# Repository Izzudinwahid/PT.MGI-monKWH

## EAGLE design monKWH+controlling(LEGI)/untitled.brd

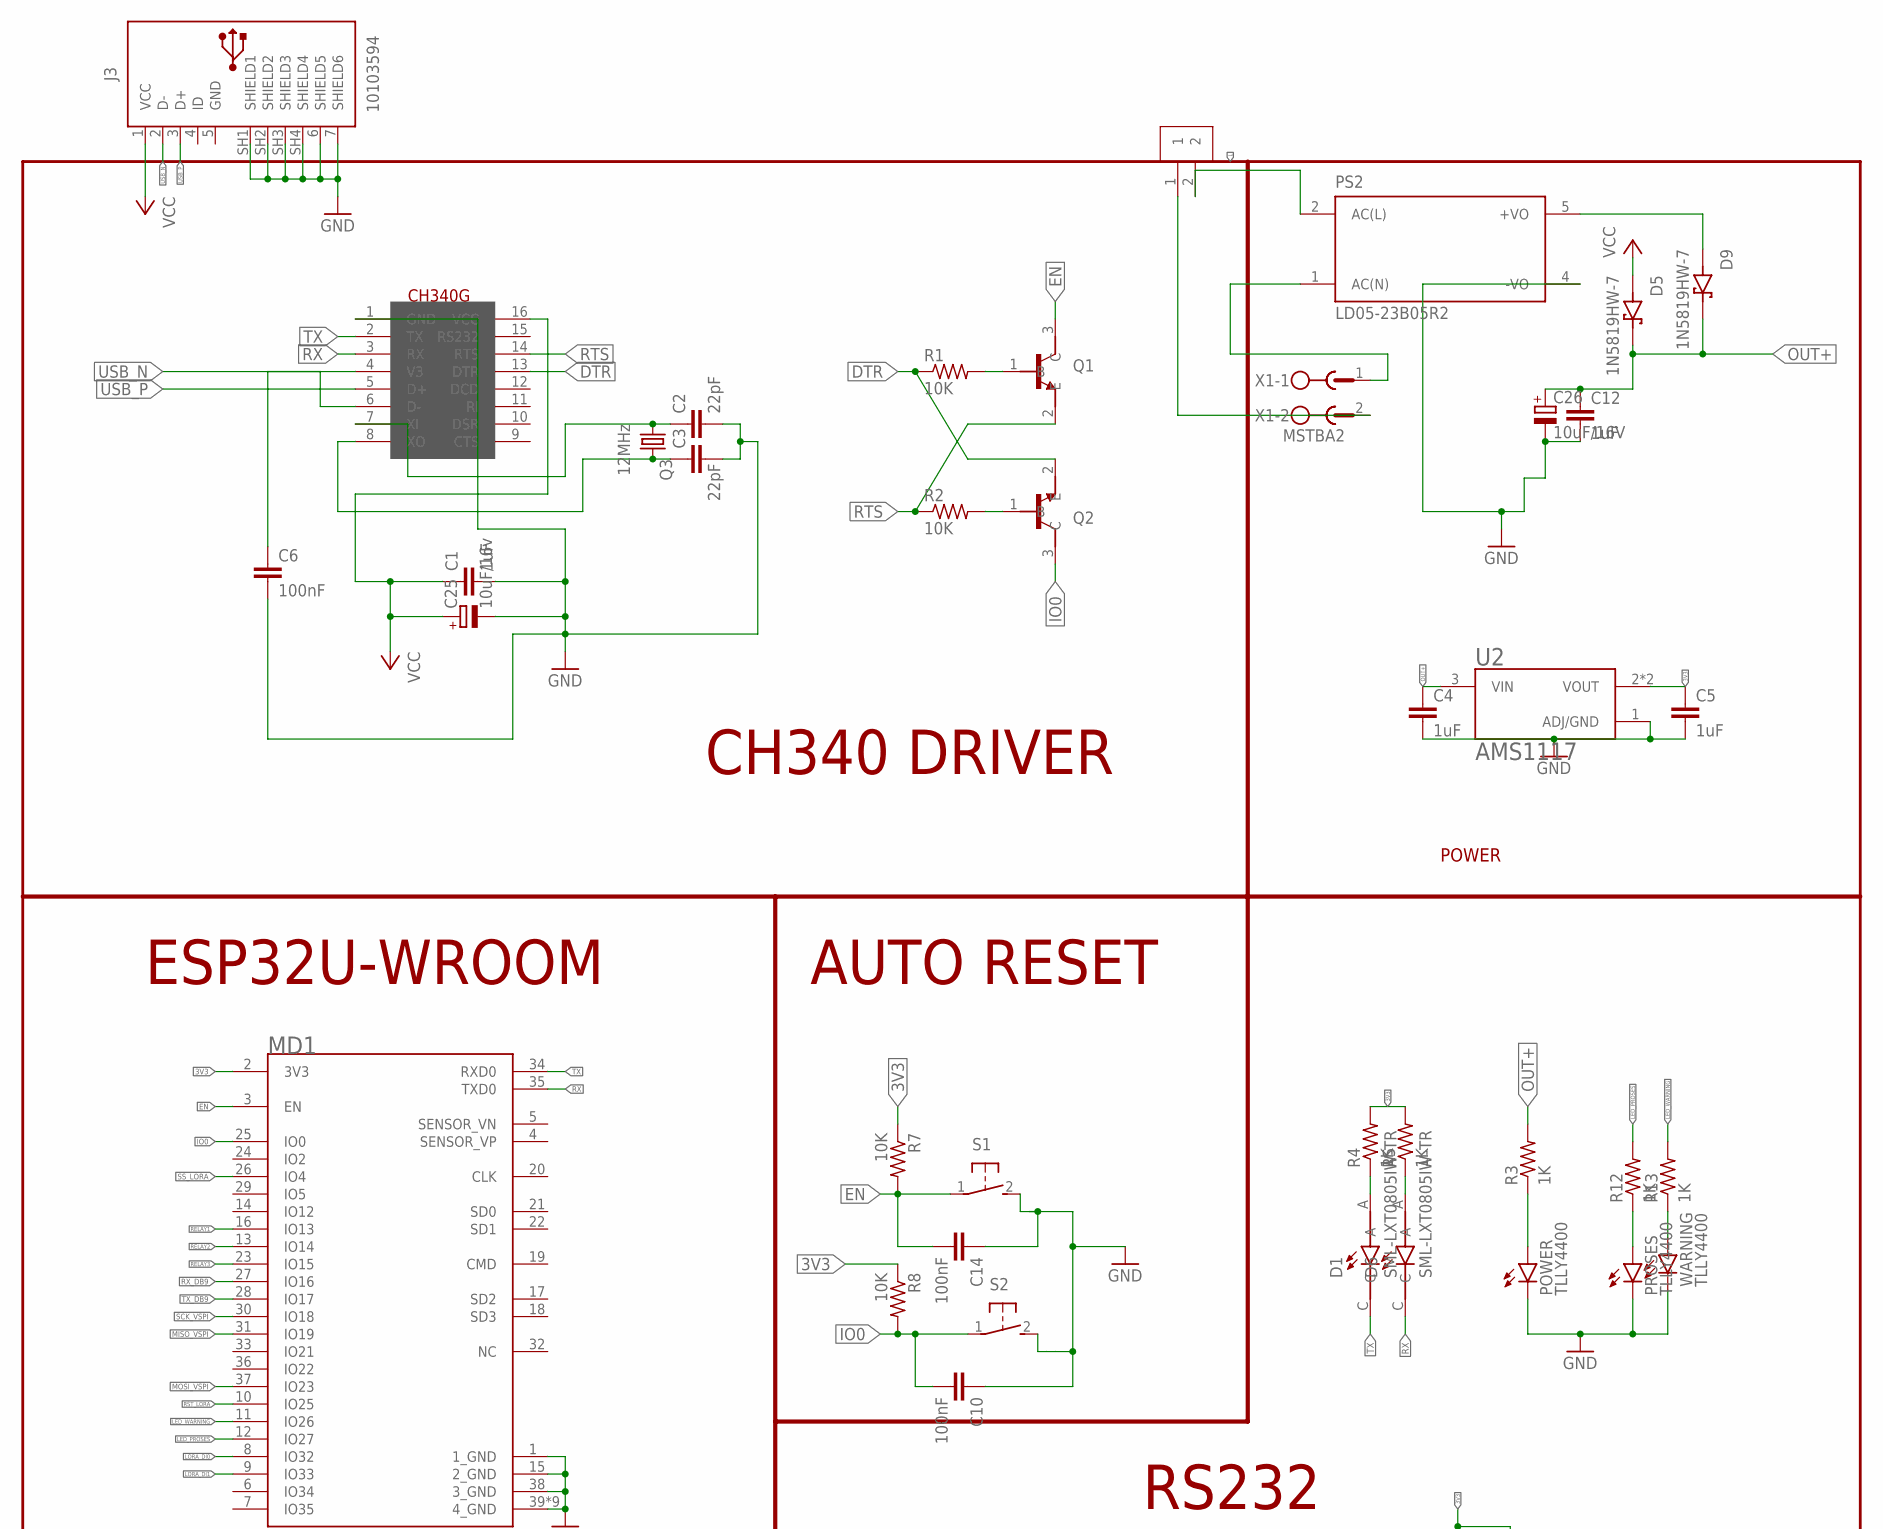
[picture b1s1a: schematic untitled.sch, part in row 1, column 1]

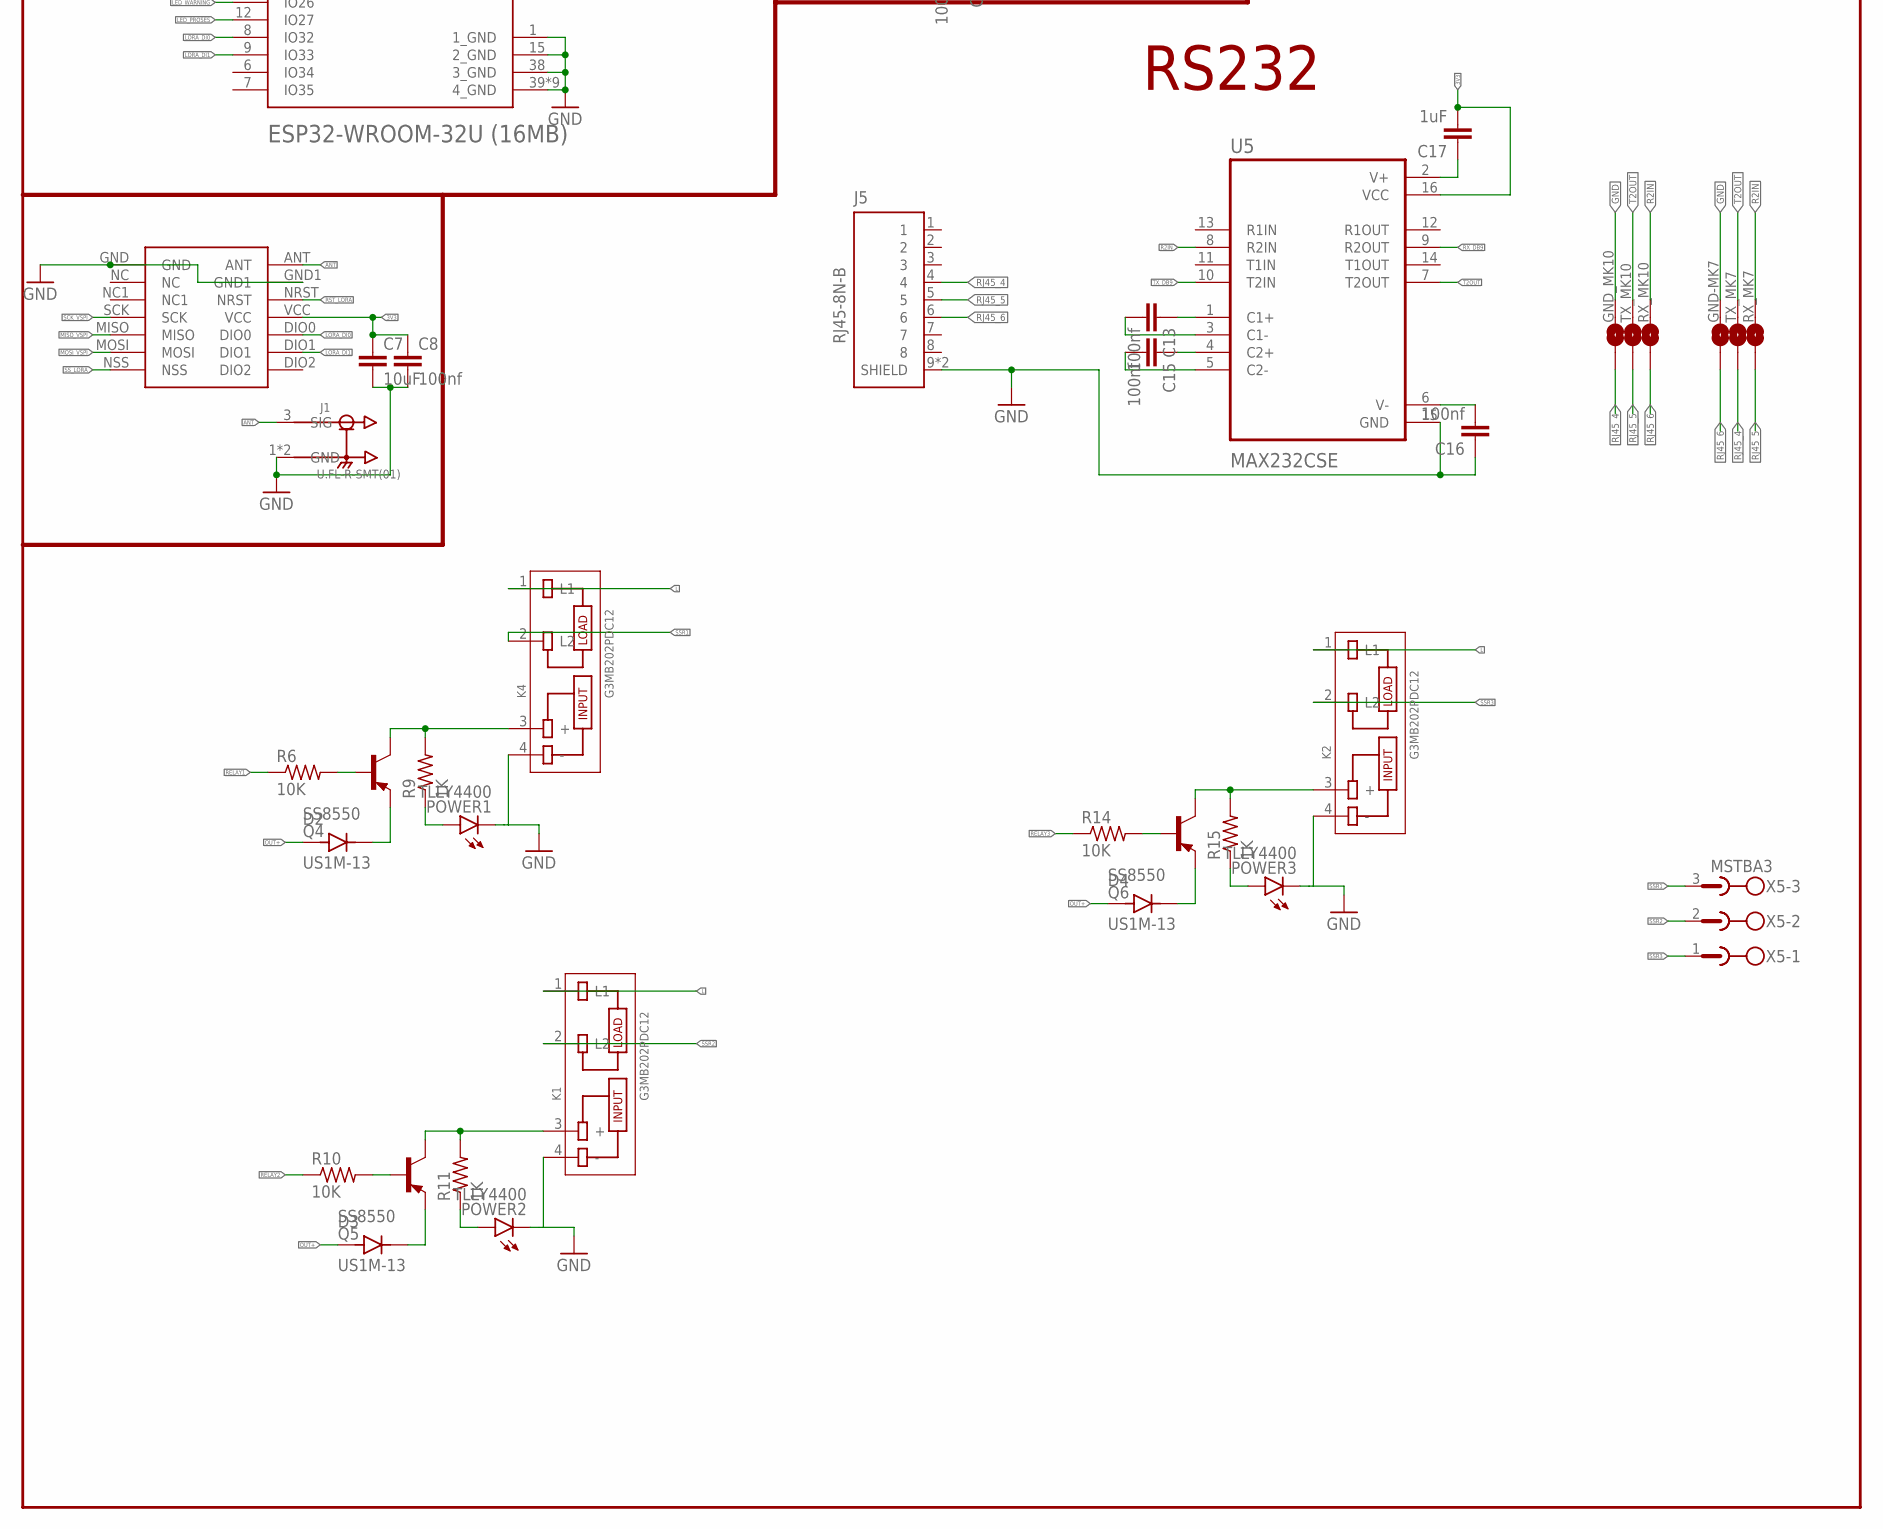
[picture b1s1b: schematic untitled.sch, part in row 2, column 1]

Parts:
C1, C4, C5, C12: 1uF; C0805K
C2, C3: 22pF; C0805K
C6, C10, C14: 100nF; C0805K
C7: 10uF; C0805
C8, C13, C15, C16: 100nf; C0805
C17: 1uF; C0805
C25: 10uF/16v; 153CLV-0505
C26: 10uF/16V; 153CLV-0505
D1, D6: SML-LXT0805IW-TR; LEDC2012X120N
D2, D3, D4: US1M-13; DIOM5226X240N
D5, D9: 1N5819HW-7; SOD3715X145N
FUSE-KOTAK1: FUSE-KOTAK
GND-MK7: 1X02-SJ-NO
GND_MK10: 1X02-SJ-NO
J1: U.FL-R-SMT(01); HRS_U.FL-R-SMT(01)
J3: 10103594
J5: RJ45-8N-B; TE_RJ45-8N-B
K1, K2, K4: G3MB202PDC12; RELAY_G3MB202PDC12
LORA-NICERF-V1: LORA-NICERF-V2
MD1: ESPRESSIF_SYSTEMS_ESP32-WROOM-32U_16MBESPRESSIF_S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; ESPRESSIF_SYSTEMS_ESP32-WROOM-32U_16MB_0
POWER, POWER1, POWER2, POWER3: TLLY4400; LED3MM
PROSES: TLLY4400; LED3MM
PS2: LD05-23B05R2; CONV_LD05-23B05R2
Q1, Q2: MMBT3904; SOT95P240X120-3N
Q3: 12MHz; SM49
Q4, Q5, Q6: SS8550; SOT-23_BEC
R1, R2, R6, R7, R8, R10, R14: 10K; M0805
R3, R4, R5, R9, R11, R12, R13, R15: 1K; M0805
RX_MK7, RX_MK10: 1X02-SJ-NO
S1, S2: 31-XX; B3F-31XX
TX_MK7, TX_MK10: 1X02-SJ-NO
U2: AMS1117; SOT229P700X180-4N
U5: MAX232CSE; SOIC127P600X175-16N
U$2: CH340G; SOIC16
WARNING: TLLY4400; LED3MM
X1: MSTBA2
X5: MSTBA3

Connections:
3V3: C5.1, C7.1, C8.1, C17.2, LORA-NICERF-V1.VCC, MD1.2 (3V3), R4.2, R5.2, R7.1, R8.1, U2.2 (VOUT), U2.4 (VOUT), U5.16 (VCC)
ANT: J1.3 (SIG), LORA-NICERF-V1.ANT
DTR: Q2.2 (E), R1.1, U$2.13 (DTR)
EN: C14.2, MD1.3 (EN), Q1.3 (C), R7.2, S1.1
GND: C1.2, C2.2, C3.2, C4.2, C5.2, C6.2, C7.2, C8.2, C10.1, C12.2, C14.1, C16.1, C25.-, C26.-, GND-MK7.2, GND_MK10.2, J1.1 (GND), J1.2 (GND), J3.5 (GND), J3.6 (SHIELD5), J3.7 (SHIELD6), J3.SH1 (SHIELD1), J3.SH2 (SHIELD2), J3.SH3 (SHIELD3), J3.SH4 (SHIELD4), J5.9 (SHIELD), J5.10 (SHIELD), K1.4 (-), K2.4 (-), K4.4 (-), LORA-NICERF-V1.GND, LORA-NICERF-V1.GND1, MD1.1 (1_GND), MD1.15 (2_GND), MD1.38 (3_GND), MD1.39 (4_GND), MD1.39-2 (4_GND), MD1.39-3 (4_GND), MD1.39-4 (4_GND), MD1.39-5 (4_GND), MD1.39-6 (4_GND), MD1.39-7 (4_GND), MD1.39-8 (4_GND), MD1.39-9 (4_GND), POWER.K (C), POWER1.K (C), POWER2.K (C), POWER3.K (C), PROSES.K (C), PS2.4 (-VO), S1.2 (S), S2.2 (S), U2.1 (ADJ/GND), U5.15 (GND), U$2.1 (GND), WARNING.K (C)
IO0: C10.2, MD1.25 (IO0), Q2.3 (C), R8.2, S2.1
L: FUSE-KOTAK1.2, K1.1 (L1), K2.1 (L1), K4.1 (L1), PS2.2 (AC(L))
LED_PROSES: MD1.12 (IO27), R12.2
LED_WARNING: MD1.11 (IO26), R13.2
LORA_DI0: LORA-NICERF-V1.DIO0, MD1.8 (IO32)
LORA_DI1: LORA-NICERF-V1.DIO1, MD1.9 (IO33)
MISO_VSPI: LORA-NICERF-V1.MISO, MD1.31 (IO19)
MOSI_VSPI: LORA-NICERF-V1.MOSI, MD1.37 (IO23)
unnamed: C2.1, Q3.1, U$2.7 (XI)
unnamed: C3.1, Q3.2, U$2.8 (XO)
unnamed: POWER.A, R3.1
unnamed: Q1.1 (B), R1.2
unnamed: Q2.1 (B), R2.2
unnamed: D2.C (K), Q4.E
unnamed: Q4.B, R6.2
unnamed: D1.A, R4.1
unnamed: D6.A, R5.1
unnamed: C13.1, U5.1 (C1+)
unnamed: PS2.1 (AC(N)), X1.1
unnamed: C6.1, U$2.4 (V3)
unnamed: C13.2, U5.3 (C1-)
unnamed: K4.3 (+), Q4.C, R9.2
unnamed: D9.A, PS2.5 (+VO)
unnamed: FUSE-KOTAK1.1, X1.2
unnamed: POWER1.A, R9.1
unnamed: C15.1, U5.4 (C2+)
unnamed: D3.C (K), Q5.E
unnamed: Q5.B, R10.2
unnamed: C15.2, U5.5 (C2-)
unnamed: PROSES.A, R12.1
unnamed: C17.1, U5.2 (V+)
unnamed: C16.2, U5.6 (V-)
unnamed: R13.1, WARNING.A
unnamed: K1.3 (+), Q5.C, R11.2
unnamed: POWER2.A, R11.1
unnamed: D4.C (K), Q6.E
unnamed: Q6.B, R14.2
unnamed: K2.3 (+), Q6.C, R15.2
unnamed: POWER3.A, R15.1
OUT+: C4.1, C12.1, C26.+, D2.A, D3.A, D4.A, D5.C (K), D9.C (K), R3.2, U2.3 (VIN)
R2IN: RX_MK7.2, RX_MK10.2, U5.8 (R2IN)
RELAY1: MD1.16 (IO13), R6.1
RELAY2: MD1.13 (IO14), R10.1
RELAY3: MD1.23 (IO15), R14.1
RJ45_4: GND_MK10.1, J5.4, TX_MK7.1
RJ45_5: J5.5, RX_MK7.1, TX_MK10.1
RJ45_6: GND-MK7.1, J5.6, RX_MK10.1
RST_LORA: LORA-NICERF-V1.NRST, MD1.10 (IO25)
RTS: Q1.2 (E), R2.1, U$2.14 (RTS)
RX: D6.C, MD1.35 (TXD0), U$2.3 (RX)
RX_DB9: MD1.27 (IO16), U5.9 (R2OUT)
SCK_VSPI: LORA-NICERF-V1.SCK, MD1.30 (IO18)
SSR1: K4.2 (L2), X5.3
SSR2: K1.2 (L2), X5.2
SSR3: K2.2 (L2), X5.1
SS_LORA: LORA-NICERF-V1.NSS, MD1.26 (IO4)
T2OUT: TX_MK7.2, TX_MK10.2, U5.7 (T2OUT)
TX: D1.C, MD1.34 (RXD0), U$2.2 (TX)
TX_DB9: MD1.28 (IO17), U5.10 (T2IN)
USB_N: J3.2 (D-), U$2.6 (D-)
USB_P: J3.3 (D+), U$2.5 (D+)
VCC: C1.1, C25.+, D5.A, J3.1 (VCC), U$2.16 (VCC)

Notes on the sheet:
CH340 DRIVER
POWER
ESP32U-WROOM
AUTO RESET
RS232

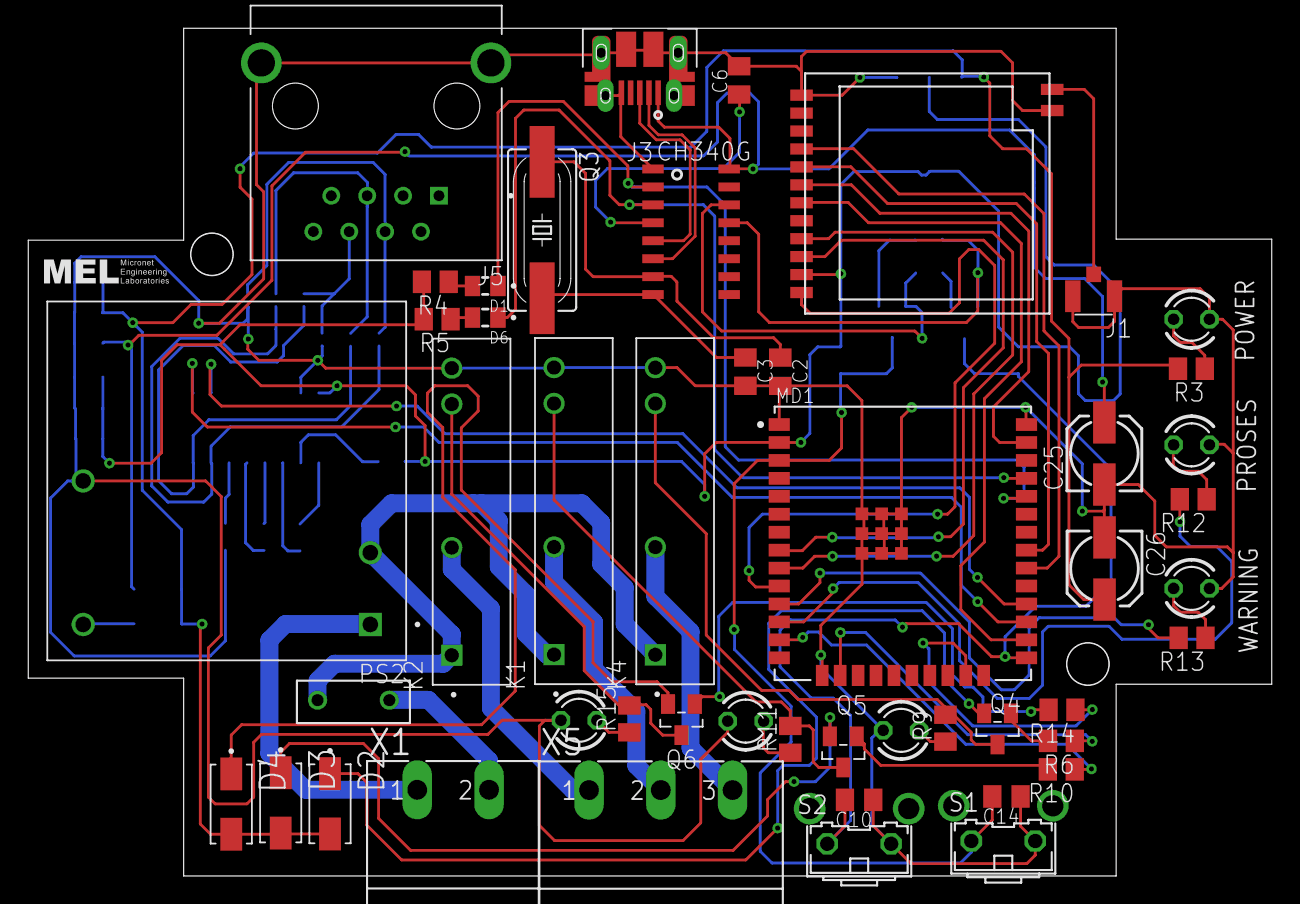
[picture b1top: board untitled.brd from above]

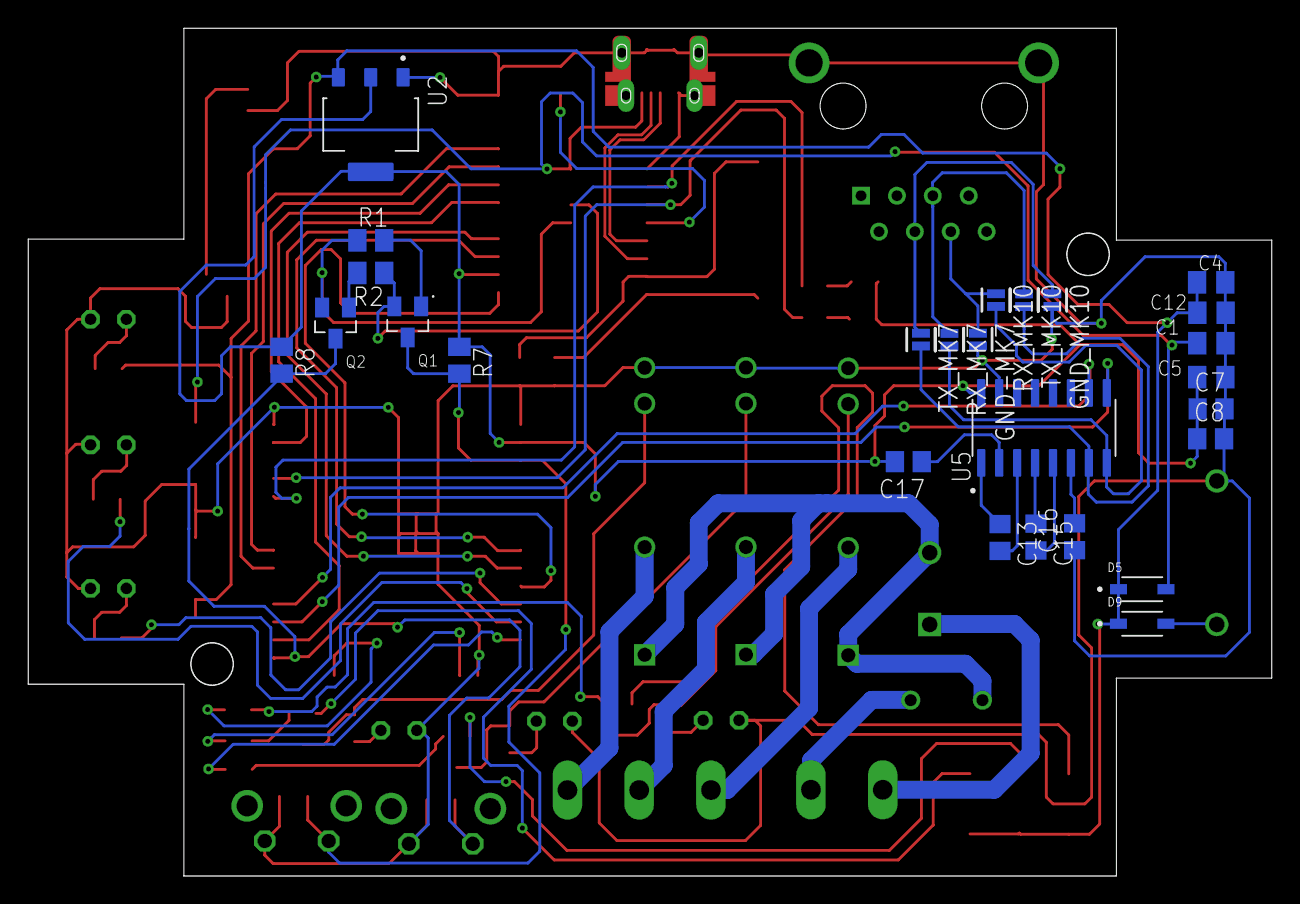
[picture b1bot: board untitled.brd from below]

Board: 2 copper layers, 88.0 x 60.0 mm, 74 parts (26 on the bottom side), 67 nets.

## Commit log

2022-08-18 PCB mohKWH
2022-08-25 revisi .sch dan membuat.brd
2022-08-25 revisi .brd
2022-09-02 penambahan komponen
2022-09-26 membuat desain PCB dengan GPS
2022-09-30 revisi rangkaian
2022-09-30 revisi jeck DC
2022-10-11 rangkaian Versi2
2022-10-17 edited 17 oct
    - ganti kapasitor
    - tambah jumper tipe rs232
2022-11-10 change mini usb to micro usb
2022-12-02 revisi power supply
2023-04-03 pembuatan PCB Halim
2023-04-05 pengajuan komponen monkhw-HALIM
2023-05-17 membuat PCB LEGI versi HALIM dengan komunikasi LoRa

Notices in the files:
parts and their libraries:
SparkFun-Connectors: Licensing: Creative Commons ShareAlike 4.0 International - https://creativecommons.org/licenses/by-sa/4.0
